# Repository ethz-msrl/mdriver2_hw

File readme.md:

# MDriver2 Hardware
This repository contains the hardware design files of the `MDriver2` project.
## Control Hardware

## Power Hardware

## Experimental Setup Overview

- The input diode `D1` is optional and used to protect the supply `V1`.
- The charge resistor `R1` is used to limit excessive inrush current to the capcacitor bank but may not be needed for all supplies.
- The DC link voltage `VH` is monitored using an isolated DC measurement from the `capbank` PCB. Voltage values are transmitted via delta-sigma modulation to the microcontroller.

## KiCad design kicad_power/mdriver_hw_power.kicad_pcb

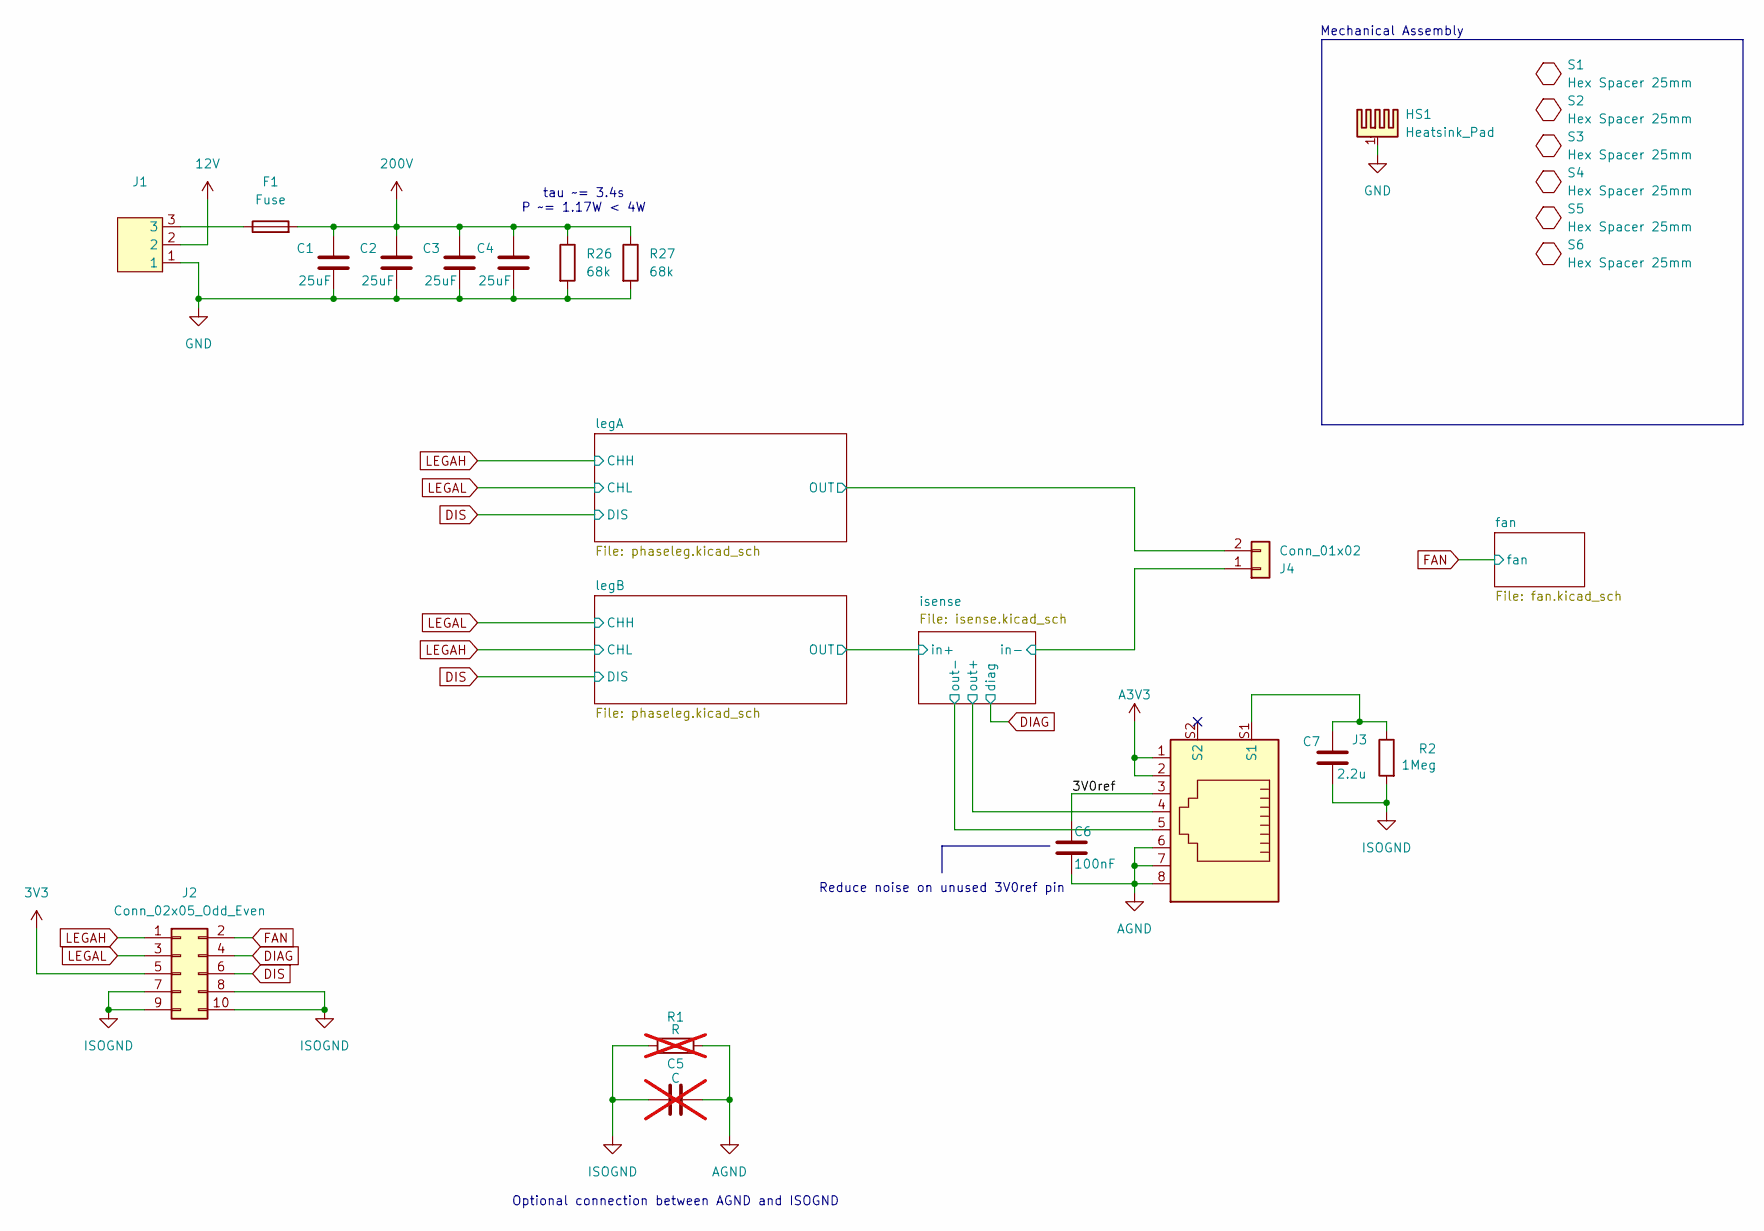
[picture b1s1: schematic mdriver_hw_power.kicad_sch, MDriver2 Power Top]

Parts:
C1, C2, C3, C4: 25uF; film_cap_25uF; Partno FB37F38I0256KC
C5: C; C_0402_1005Metric; not fitted
C6: 100nF; C_0402_1005Metric; Partno C0402C104K4RECAUTO; JLCPCB C1525
C7: 2.2u; C_0603_1608Metric; Partno CGA3E1X7S1C225K080AE; JLCPCB CL10A225KA8NNNC
F1: Fuse; fuse; Partno 0031.8225
HS1: Heatsink_Pad; heatsink_assman; Partno V5583K
J1: CONN_1148070000_WED; Partno 1148070000
J2: Conn_02x05_Odd_Even; 10pin_data_connector; Partno 3010-10-003-13-00
J3: J_Wurth_WR-MJ_634008149821; Partno 634008149821
J4: Conn_01x02; weidmuller_20A_2pin; Partno 1148030000
R1: R; R_0402_1005Metric; not fitted
R2: 1Meg; R_0402_1005Metric; Partno CRCW04021M00FKED; JLCPCB C26083
R26, R27: 68k; R_2512_6332Metric; Partno 4-2176331-7
S1, S2, S3, S4, S5, S6: Hex Spacer 25mm; hex_spacer; Partno 25506

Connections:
3V3: J2.5; also elsewhere on the board
12V: J1.2; also elsewhere on the board
200V: C1.1, C2.1, C3.1, C4.1, F1.2, R26.1, R27.1; also elsewhere on the board
/3V0ref: C6.1, J3.3
/isense/in-: J4.1; also elsewhere on the board
/isense/out+: J3.4; also elsewhere on the board
/isense/out-: J3.5; also elsewhere on the board
/legA/OUT: J4.2; also elsewhere on the board
A3V3: J3.1, J3.2; also elsewhere on the board
AGND: C5.2, C6.2, J3.6, J3.7, J3.8, R1.2; also elsewhere on the board
DIAG: J2.4; also elsewhere on the board
DIS: J2.6; also elsewhere on the board
FAN: J2.2; also elsewhere on the board
GND: C1.2, C2.2, C3.2, C4.2, HS1.1, J1.1, R26.2, R27.2; also elsewhere on the board
ISOGND: C5.1, C7.2, J2.7, J2.8, J2.9, J2.10, R1.1, R2.2; also elsewhere on the board
LEGAH: J2.1; also elsewhere on the board
LEGAL: J2.3; also elsewhere on the board
unnamed: C7.1, J3.S1, R2.1
unnamed: F1.1, J1.3

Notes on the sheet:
Optional connection between AGND and ISOGND
tau ~= 3.4s P ~= 1.17W < 4W
Mechanical Assembly
Reduce noise on unused 3V0ref pin

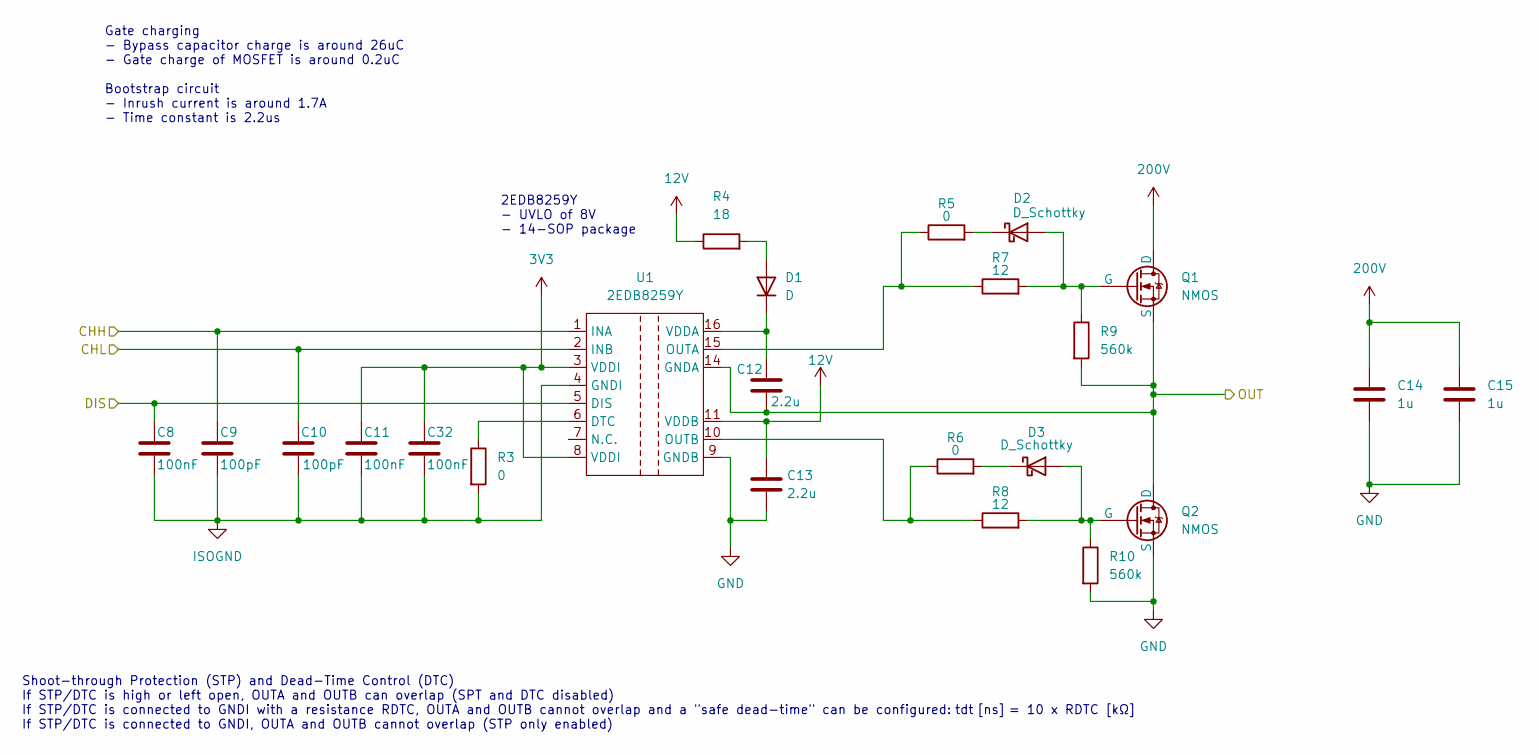
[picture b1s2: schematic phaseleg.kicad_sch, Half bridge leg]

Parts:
C8, C11, C32: 100nF; C_0402_1005Metric; Partno C0402C104K4RECAUTO; JLCPCB C1525
C9, C10: 100pF; C_0402_1005Metric; Partno VJ0402A101JXACW1BC; JLCPCB C26409
C12, C13: 2.2u; C_0603_1608Metric; Partno CGA3E1X7S1C225K080AE; JLCPCB CL10A225KA8NNNC
C14, C15: 1u; C_2220_5750Metric_Pad1.97x5.40mm_HandSolder; Partno 885342214001
D1: D; D_SOD-123F; Partno ES1JFL; JLCPCB C719809
D2, D3: D_Schottky; D_SOD-323F; Partno SD107WS-7-F; JLCPCB C124210
Q1, Q2: NMOS; TO-247-3_Vertical; Partno IPW60R024P7XKSA1
R3: 0; R_0402_1005Metric; Partno RCA04020000ZSED; JLCPCB C17168
R4: 18; R_1206_3216Metric; Partno CRGP1206F18R
R5, R6: 0; R_0603_1608Metric; Partno CRCW06030000ZSTB; JLCPCB C25165
R7, R8: 12; R_0603_1608Metric; Partno ERJPA3F12R0V
R9, R10: 560k; R_0402_1005Metric; Partno CRGCQ0402F560K; JLCPCB C15785
U1: 2EDB8259Y; SOIC-16; Partno 2EDB8259YXUMA1

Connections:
3V3: C11.1, C32.1, U1.3 (VDDI), U1.8 (VDDI); also elsewhere on the board
12V: C13.1, R4.1, U1.11 (VDDB); also elsewhere on the board
200V: C14.1, C15.1, Q1.2 (D); also elsewhere on the board
/legA/OUT: C12.2, Q1.3 (S), Q2.2 (D), R9.2, U1.14 (GNDA); also elsewhere on the board
DIS: C8.1, U1.5 (DIS); also elsewhere on the board
GND: C13.2, C14.2, C15.2, Q2.3 (S), R10.2, U1.9 (GNDB); also elsewhere on the board
ISOGND: C8.2, C9.2, C10.2, C11.2, C32.2, R3.2, U1.4 (GNDI); also elsewhere on the board
LEGAH: C9.1, U1.1 (INA); also elsewhere on the board
LEGAL: C10.1, U1.2 (INB); also elsewhere on the board
unnamed: D1.2 (A), R4.2
unnamed: C12.1, D1.1 (K), U1.16 (VDDA)
unnamed: D2.2 (A), Q1.1 (G), R7.2, R9.1
unnamed: D2.1 (K), R5.2
unnamed: D3.2 (A), Q2.1 (G), R8.2, R10.1
unnamed: D3.1 (K), R6.2
unnamed: R3.1, U1.6 (DTC)
unnamed: R5.1, R7.1, U1.15 (OUTA)
unnamed: R6.1, R8.1, U1.10 (OUTB)

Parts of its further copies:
C16, C19, C33: 100nF; C_0402_1005Metric; Partno C0402C104K4RECAUTO; JLCPCB C1525
C17, C18: 100pF; C_0402_1005Metric; Partno VJ0402A101JXACW1BC; JLCPCB C26409
C20, C21: 2.2u; C_0603_1608Metric; Partno CGA3E1X7S1C225K080AE; JLCPCB CL10A225KA8NNNC
C22, C23: 1u; C_2220_5750Metric_Pad1.97x5.40mm_HandSolder; Partno 885342214001
D4: D; D_SOD-123F; Partno ES1JFL; JLCPCB C719809
D5, D6: D_Schottky; D_SOD-323F; Partno SD107WS-7-F; JLCPCB C124210
Q3, Q4: NMOS; TO-247-3_Vertical; Partno IPW60R024P7XKSA1
R11: 0; R_0402_1005Metric; Partno RCA04020000ZSED; JLCPCB C17168
R12: 18; R_1206_3216Metric; Partno CRGP1206F18R
R13: 0; R_0603_1608Metric; Partno CRCW06030000ZSTB; JLCPCB C25165
R15: 12; R_0603_1608Metric; Partno ERJPA3F12R0V
R17, R18: 560k; R_0402_1005Metric; Partno CRGCQ0402F560K; JLCPCB C15785
U2: 2EDB8259Y; SOIC-16; Partno 2EDB8259YXUMA1

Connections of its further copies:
3V3: C19.1, C33.1, U2.3 (VDDI), U2.8 (VDDI); also elsewhere on the board
12V: C21.1, R12.1, U2.11 (VDDB); also elsewhere on the board
200V: C22.1, C23.1, Q3.2 (D); also elsewhere on the board
/isense/in+: C20.2, Q3.3 (S), Q4.2 (D), R17.2, U2.14 (GNDA); also elsewhere on the board
DIS: C16.1, U2.5 (DIS); also elsewhere on the board
GND: C21.2, C22.2, C23.2, Q4.3 (S), R18.2, U2.9 (GNDB); also elsewhere on the board
ISOGND: C16.2, C17.2, C18.2, C19.2, C33.2, R11.2, U2.4 (GNDI); also elsewhere on the board
LEGAH: C18.1, U2.2 (INB); also elsewhere on the board
LEGAL: C17.1, U2.1 (INA); also elsewhere on the board
unnamed: D4.2 (A), R12.2
unnamed: C20.1, D4.1 (K), U2.16 (VDDA)
unnamed: D5.2 (A), Q3.1 (G), R15.2, R17.1
unnamed: D5.1 (K), R13.2
unnamed 30: D6.2 (A), Q4.1 (G), R18.1; also elsewhere on the board
unnamed 31: D6.1 (K); also elsewhere on the board
unnamed: R11.1, U2.6 (DTC)
unnamed: R13.1, R15.1, U2.15 (OUTA)
unnamed 45: U2.10 (OUTB); also elsewhere on the board

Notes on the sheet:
2EDB8259Y - UVLO of 8V - 14-SOP package
Shoot-through Protection (STP) and Dead-Time Control (DTC) If STP/DTC is high or left open, OUTA and OUTB can overlap (SPT and DTC disabled) If STP/DTC is connected to GNDI with a resistance RDTC, OUTA and OUTB cannot overlap and a "safe dead-time" can be configured: tdt [ns] = 10 x RDTC [kΩ] If ST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
Gate charging - Bypass capacitor charge is around 26uC - Gate charge of MOSFET is around 0.2uC Bootstrap circuit - Inrush current is around 1.7A - Time constant is 2.2us

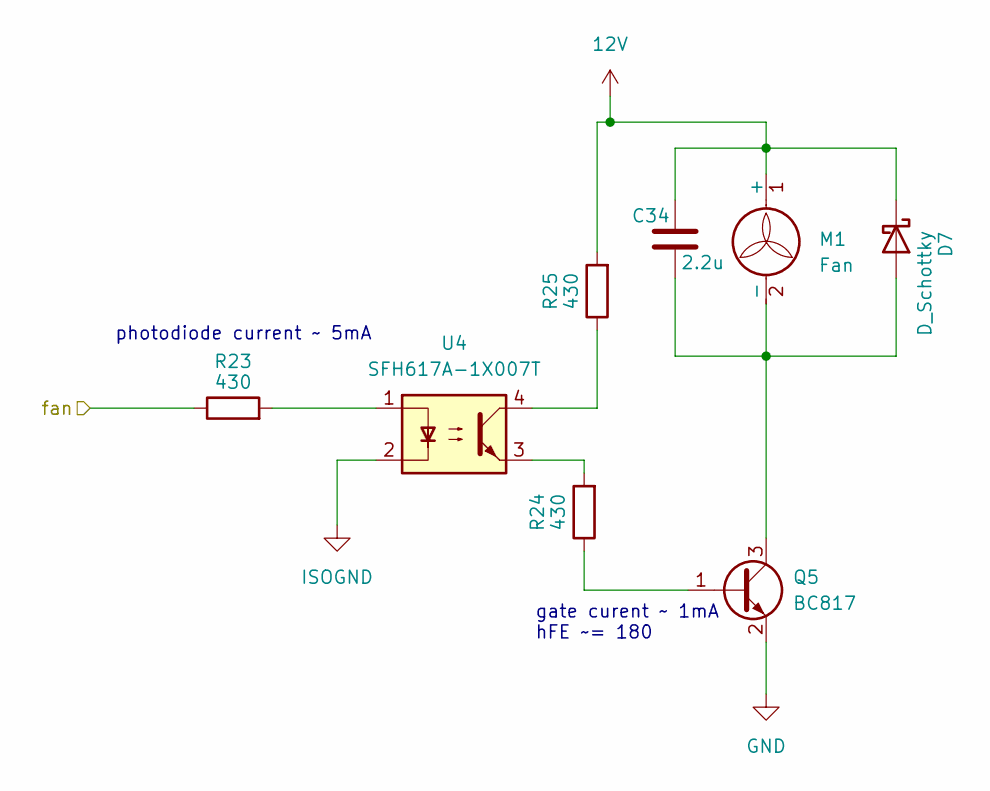
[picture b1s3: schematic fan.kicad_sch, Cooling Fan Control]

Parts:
C34: 2.2u; C_0603_1608Metric; Partno CGA3E1X7S1C225K080AE; JLCPCB CL10A225KA8NNNC
D7: D_Schottky; D_SOD-323F; Partno SD107WS-7-F; JLCPCB C124210
M1: Fan; PinHeader_1x02_P2.54mm_Vertical
Q5: BC817; SOT-23; Partno Nexperia BC817-25,235; JLCPCB C2137
R23, R24, R25: 430; R_0603_1608Metric; Partno ERJ-PA3F4300V; JLCPCB C23170
U4: SFH617A-1X007T; SMDIP-4_W9.53mm_Clearance8mm; Partno SFH617A-1X007T

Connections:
12V: C34.1, D7.1 (K), M1.1 (+), R25.2; also elsewhere on the board
FAN: R23.1; also elsewhere on the board
GND: Q5.2 (E); also elsewhere on the board
ISOGND: U4.2; also elsewhere on the board
unnamed: C34.2, D7.2 (A), M1.2 (-), Q5.3 (C)
unnamed: Q5.1 (B), R24.1
unnamed: R23.2, U4.1
unnamed: R24.2, U4.3
unnamed: R25.1, U4.4

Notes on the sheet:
gate curent ~ 1mA hFE ~= 180
photodiode current ~ 5mA

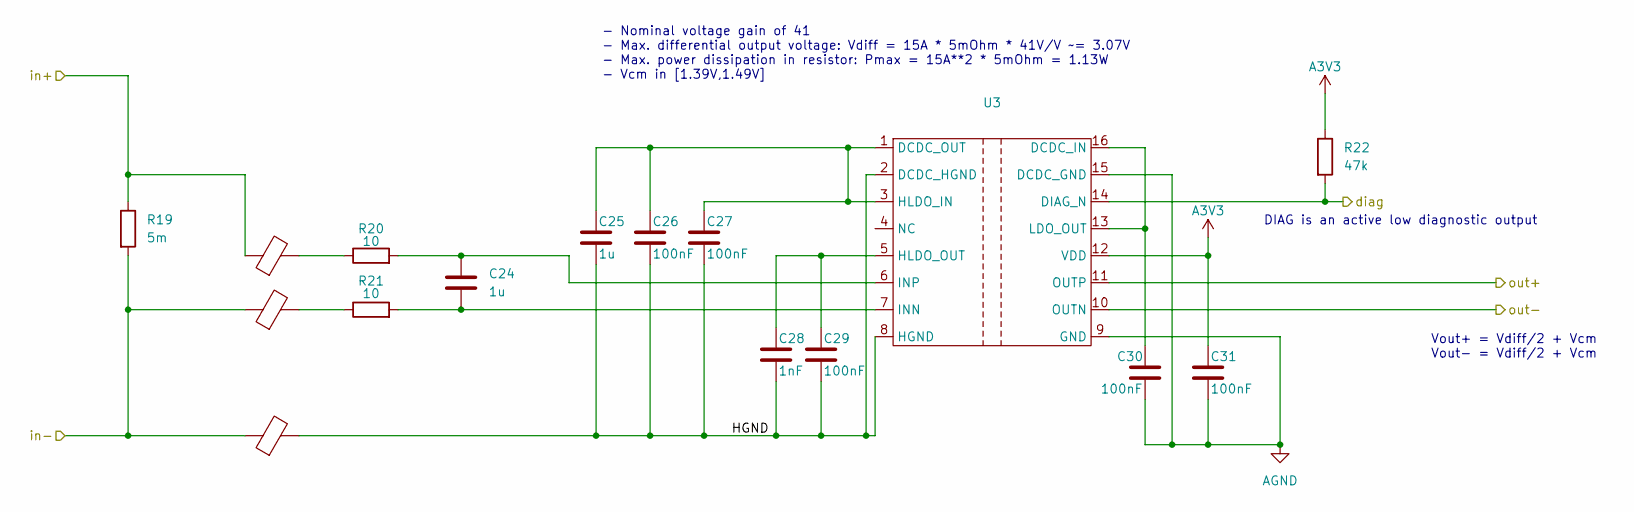
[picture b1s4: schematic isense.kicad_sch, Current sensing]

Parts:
C24, C25: 1u; C_0402_1005Metric; Partno 0402YD105KAT2A; JLCPCB C14445
C26, C27, C29, C30, C31: 100nF; C_0402_1005Metric; Partno C0402C104K4RECAUTO; JLCPCB C1525
C28: 1nF; C_0402_1005Metric; Partno CL05B102KB5NNNC; JLCPCB C1523
FB1, FB2, FB3: 2.2Ohm; L_0402_1005Metric; Partno 74269244182; JLCPCB C7038862
R19: 5m; R_2512_6332Metric_Pad1.40x3.35mm_HandSolder; Partno MCS3264R005FER; JLCPCB C108931
R20, R21: 10; R_0402_1005Metric; Partno RC0402JR-0710RL; JLCPCB C4109
R22: 47k; R_0402_1005Metric; Partno CRGP0402F47K; JLCPCB C25563
U3: AMC3302DWER; Partno AMC3302DWER; JLCPCB C4990160

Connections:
/isense/HGND: C25.2, C26.2, C27.2, C28.2, C29.2, FB3.2, U3.2 (DCDC_HGND), U3.8 (HGND)
/isense/in+: FB1.1, R19.1; also elsewhere on the board
/isense/in-: FB2.1, FB3.1, R19.2; also elsewhere on the board
/isense/out+: U3.11 (OUTP); also elsewhere on the board
/isense/out-: U3.10 (OUTN); also elsewhere on the board
A3V3: C31.1, R22.1, U3.12 (VDD); also elsewhere on the board
AGND: C30.2, C31.2, U3.9 (GND), U3.15 (DCDC_GND); also elsewhere on the board
DIAG: R22.2, U3.14 (DIAG_N); also elsewhere on the board
unnamed: FB1.2, R20.1
unnamed: FB2.2, R21.1
unnamed: C30.1, U3.13 (LDO_OUT), U3.16 (DCDC_IN)
unnamed: C25.1, C26.1, C27.1, U3.1 (DCDC_OUT), U3.3 (HLDO_IN)
unnamed: C28.1, C29.1, U3.5 (HLDO_OUT)
unnamed: C24.2, R21.2, U3.7 (INN)
unnamed: C24.1, R20.2, U3.6 (INP)

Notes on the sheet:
DIAG is an active low diagnostic output
Vout+ = Vdiff/2 + Vcm Vout- = Vdiff/2 + Vcm
- Nominal voltage gain of 41 - Max. differential output voltage: Vdiff = 15A * 5mOhm * 41V/V ~= 3.07V - Max. power dissipation in resistor: Pmax = 15A**2 * 5mOhm = 1.13W - Vcm in [1.39V,1.49V]

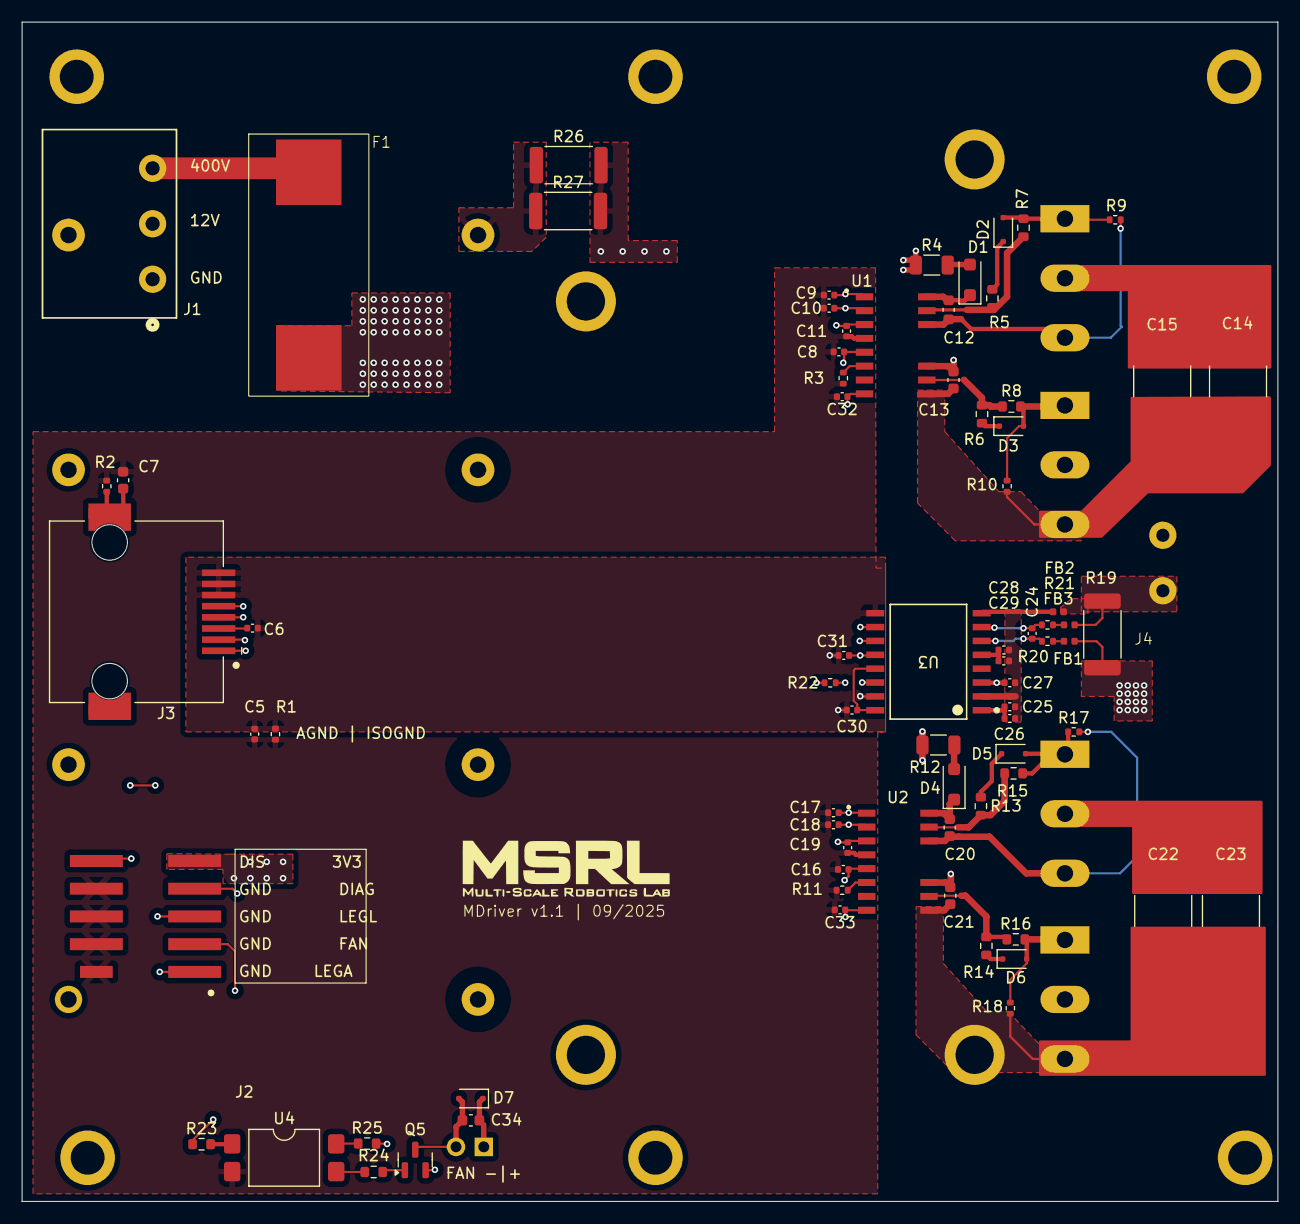
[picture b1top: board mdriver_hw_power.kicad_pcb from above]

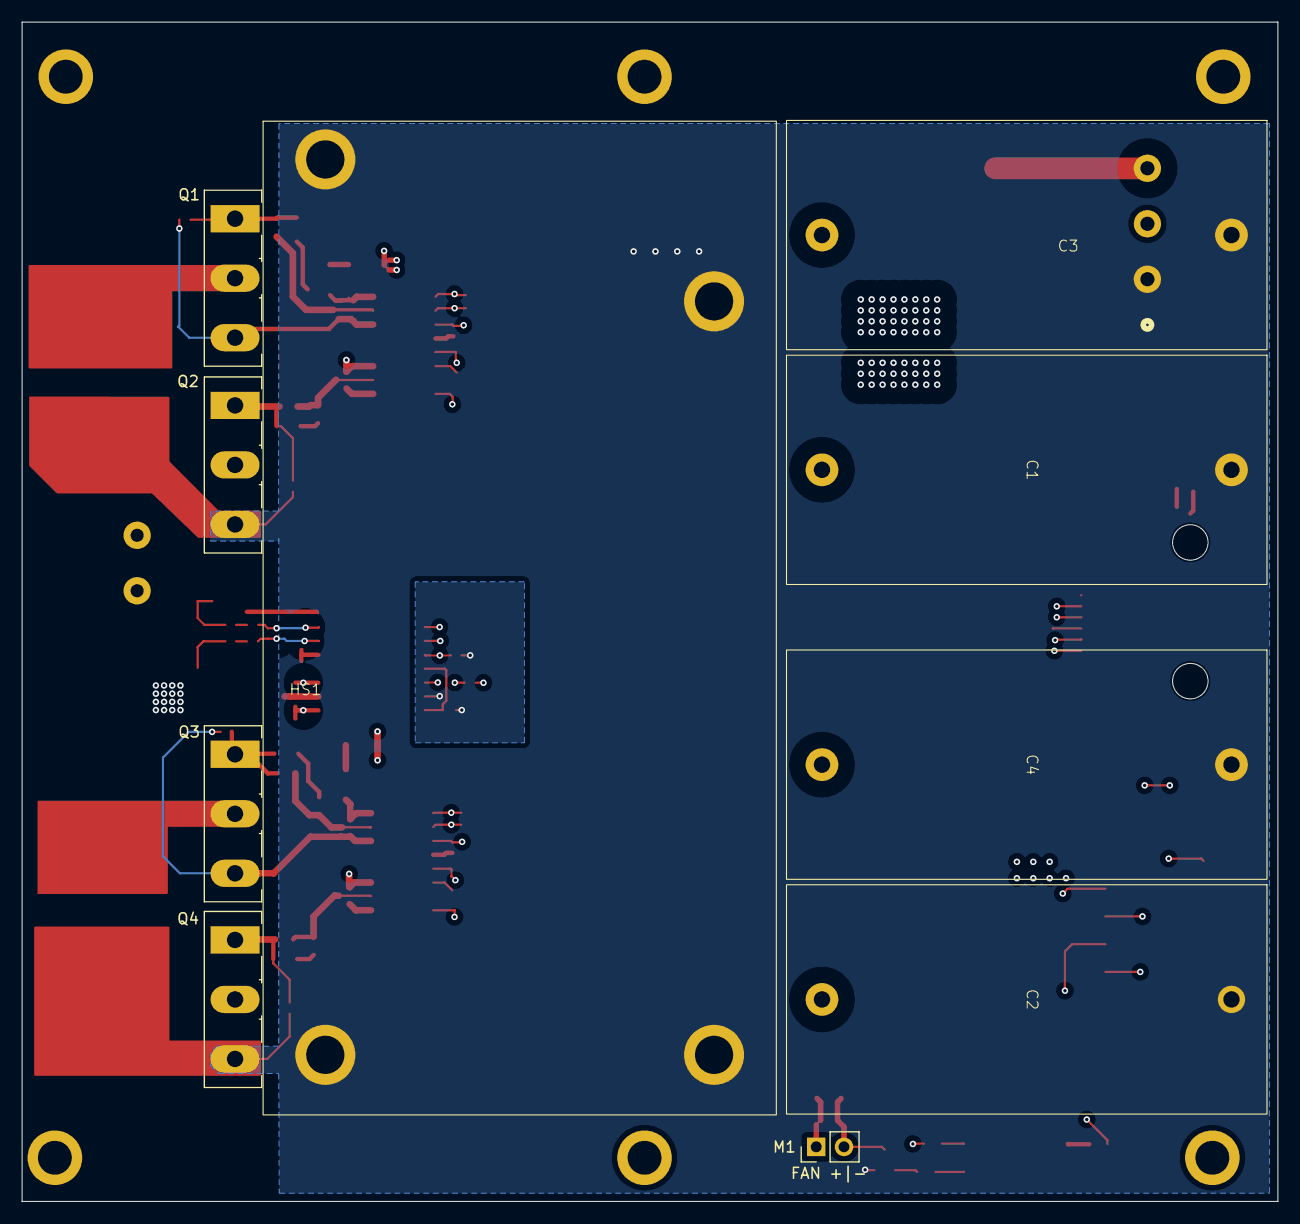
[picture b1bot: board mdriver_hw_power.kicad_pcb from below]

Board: 4 copper layers, 115.0 x 108.0 mm, 93 parts (16 on the bottom side), 51 nets.

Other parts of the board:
R14, R16: 3.3; R_0603_1608Metric

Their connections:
unnamed 30: R16.2; also elsewhere on the board
unnamed 31: R14.2; also elsewhere on the board
unnamed 45: R14.1, R16.1; also elsewhere on the board

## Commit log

2025-05-19 continue implementation of Ethernet interface
2025-05-25 completed schematic of Ethernet Section
2025-05-25 added usb/uart interface
2025-06-29 implemented layout of digital part
2025-06-30 finish initial implementation of digital layout
2025-06-30 added layout file, completed layout of ADC channels
2025-07-01 finished initial layout wo all design rules
2025-07-01 changed layout to comply with pcbway design rules
2025-07-01 finished initial version of layout
2025-07-01 added missing supplier partno, increased distance between IDC headers
2025-07-02 fixed various issues in schematics and updated layout, added datasheets
2025-07-02 added schematic and footprint library
2025-07-03 generated fabrication files
2025-07-03 adjusted via tenting
2025-07-03 adjusted BOM file
2025-07-04 fixed some issues with part description and adjusted BOM
2025-07-07 added and changed folder structure
2025-07-16 removed unused MLCCs from schematic and BOM
2025-07-16 fixed issue in parts description, footprint of RJ45 receptables, issues in BOM
2025-07-28 restructured repo and added dimensioning scripts and project for power stage part
2025-07-29 added LTSpice simulation files for ripple simulations
2025-07-31 - Added current sensing - Finished initial version of layout - Added LTSpice simulation files
2025-08-01 added missing layout file
2025-08-04 added kicad power pcb project
2025-08-05 finished initial layout of power stage in KiCAD
2025-08-05 added step files and doc file
2025-08-05 adjustment to PCB layout, created BOM file, added MOSFET gate discharge diodes
2025-08-06 introduced AGND and A3V3, ensures HV design rules
2025-08-07 finished initial version of power PCB
2025-08-22 corrected partname of AMC3302DWER
2025-09-09 added capbank pcb
2025-09-09 adjusted footprint of SMD header
2025-09-11 finished version 1.1 of power board
2025-09-12 changed description of capacitor
2025-10-16 Update project name and description in README
    adjusted readme
2025-10-16 added experimental setup description to readme
2025-10-29 replaced bootstrap resistor with anti-surge resistor
